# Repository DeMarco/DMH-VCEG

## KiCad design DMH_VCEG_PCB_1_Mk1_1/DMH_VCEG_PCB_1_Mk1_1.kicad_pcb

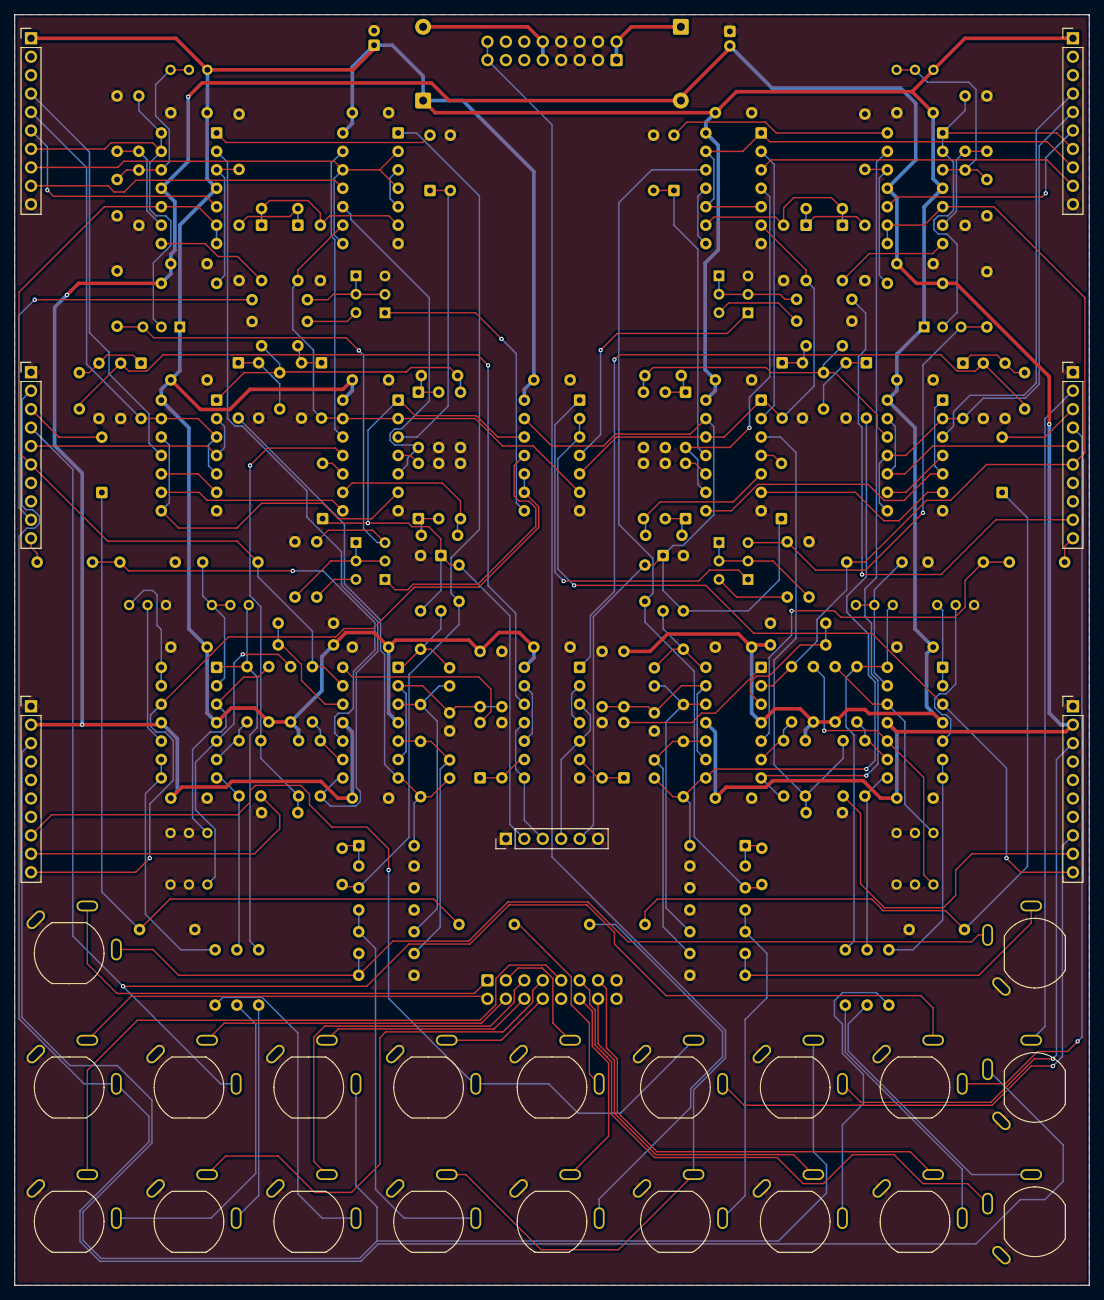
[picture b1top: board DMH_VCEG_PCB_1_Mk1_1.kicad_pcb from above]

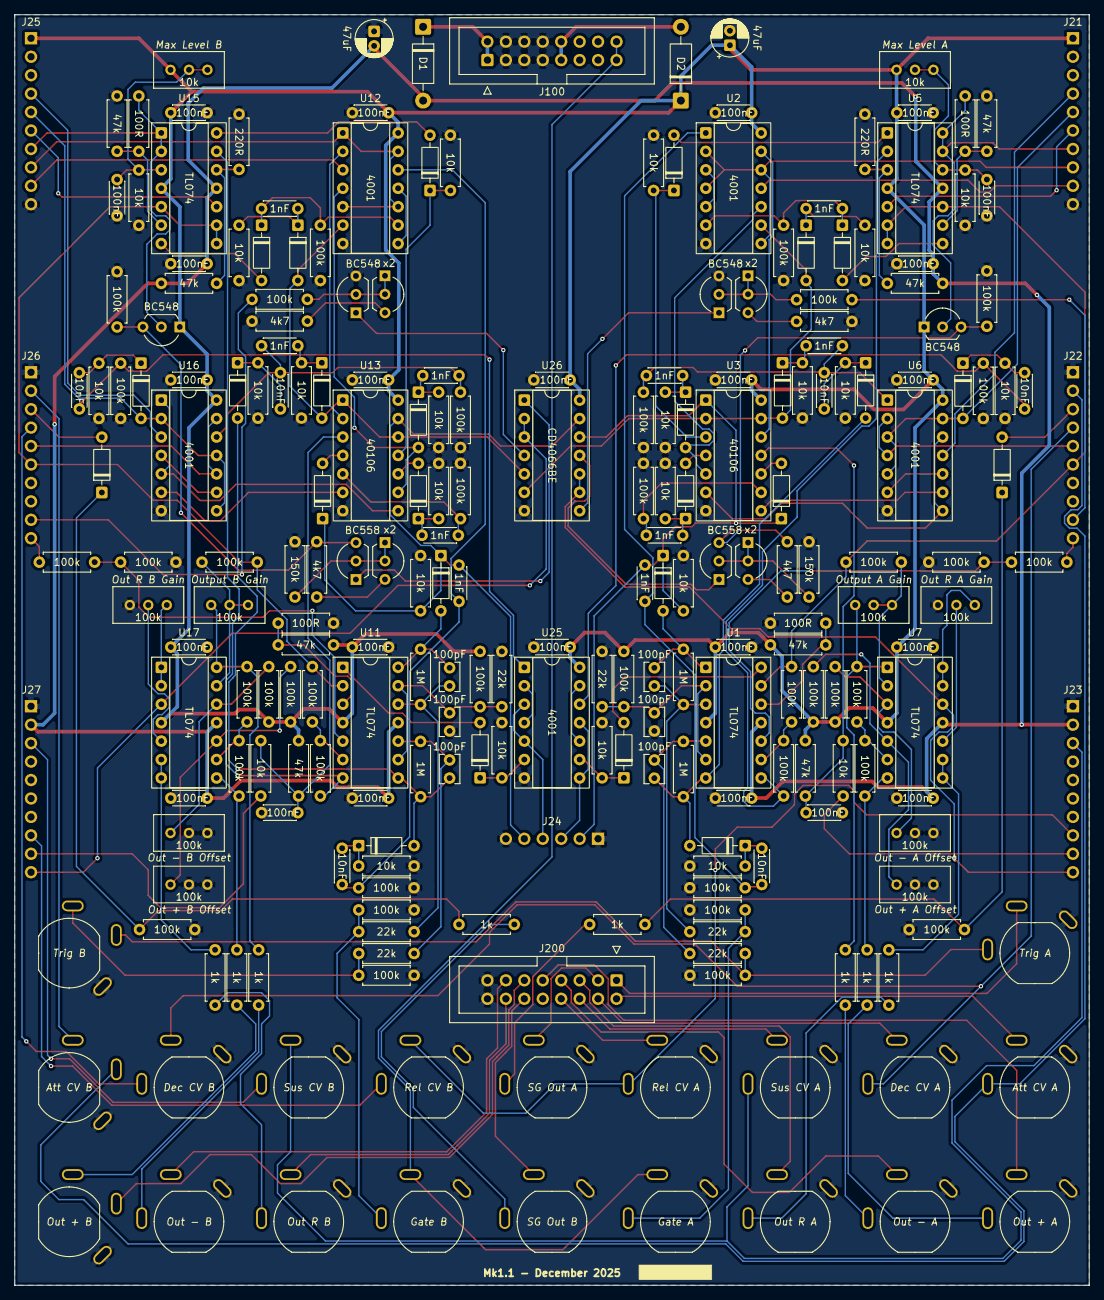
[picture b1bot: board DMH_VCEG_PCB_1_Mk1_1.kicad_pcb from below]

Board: 2 copper layers, 148.0 x 175.0 mm, 241 parts (214 on the bottom side), 183 nets.

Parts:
C1, C2: 47uF; CP_Radial_D5.0mm_P2.00mm
C3, C4, C5, C6, C8, C9, C10, C11, C12, C22, C23, C24, C25, C27, C28, C29, C30, C31, C42, C53, C58, C69, C72, C79: 100nF; C_Disc_D4.3mm_W1.9mm_P5.00mm
C41, C44, C48, C57, C60, C64: 100pF; C_Disc_D3.8mm_W2.6mm_P2.50mm
C43, C56, C59, C77, C78, C80: 10nF; C_Disc_D4.3mm_W1.9mm_P5.00mm
C46, C47, C52, C54, C55, C62, C63, C68, C70, C71: 1nF; C_Disc_D4.3mm_W1.9mm_P5.00mm
D1, D2: SB140; D_DO-41_SOD81_P10.16mm_Horizontal
D3, D4, D5, D6, D7, D12, D13, D14, D15, D16, D22, D23, D24, D25, D26, D31, D32, D33, D34, D35, D41, D42, D43, D44, D45, D46: 1N4148; D_DO-35_SOD27_P7.62mm_Horizontal
J1, J2, J3, J4, J5, J6, J7, J8, J9, J10, J11, J12, J13, J14, J15, J16, J17, J18, J19, J20: TS_Jack_6.35mm_Sw; CUI_MJ-63052A
J21, J22, J23, J25, J26, J27: Conn_01x10_PinHeader; PinHeader_1x10_P2.54mm_Vertical
J24: Conn_01x06_PinHeader; PinHeader_1x06_P2.54mm_Vertical
J100: IDC_02x08; IDC-Header_2x08_P2.54mm_Vertical_Eurorack
J200: IDC_02x08; IDC-Header_2x08_P2.54mm_Vertical_BackBone
Q1, Q2, Q17, Q18: BC558; TO-92L_Inline_Wide
Q3, Q4, Q5, Q6, Q19, Q20: BC548; TO-92L_Inline_Wide
R1, R10, R98, R107: 4k7; R_Axial_DIN0207_L6.3mm_D2.5mm_P7.62mm_Horizontal
R2, R3, R12, R14, R16, R21, R26, R36, R37, R39, R40, R42, R46, R92, R93, R94, R96, R97, R99, R100, R109, R111, R113, R118, R123, R129, R133, R134, R136, R137, R139, R143, R189, R190, R191, R193, R194, R200, R201, R202: 100k; R_Axial_DIN0207_L6.3mm_D2.5mm_P7.62mm_Horizontal
R4, R19, R34, R41, R101, R131, R138, R196: 47k; R_Axial_DIN0207_L6.3mm_D2.5mm_P7.62mm_Horizontal
R5, R23, R102, R120: 1M; R_Axial_DIN0207_L6.3mm_D2.5mm_P7.62mm_Horizontal
R6, R22, R91, R95, R103, R119, R188, R192: 1k; R_Axial_DIN0207_L6.3mm_D2.5mm_P7.62mm_Horizontal
R7, R13, R24, R25, R31, R32, R35, R38, R43, R45, R47, R104, R108, R110, R115, R116, R121, R122, R128, R132, R135, R140, R142, R144: 10k; R_Axial_DIN0207_L6.3mm_D2.5mm_P7.62mm_Horizontal
R8, R105: 150k; R_Axial_DIN0207_L6.3mm_D2.5mm_P7.62mm_Horizontal
R9, R17, R20, R106, R114, R117: 22k; R_Axial_DIN0207_L6.3mm_D2.5mm_P7.62mm_Horizontal
R33, R130, R195, R199: 100R; R_Axial_DIN0207_L6.3mm_D2.5mm_P7.62mm_Horizontal
R44, R141: 220R; R_Axial_DIN0207_L6.3mm_D2.5mm_P7.62mm_Horizontal
RV1, RV19, RV20, RV21, RV22, RV40, RV41, RV42: 100k; Potentiometer_Bourns_3296W_Vertical
RV3, RV24: 10k; Potentiometer_Bourns_3296W_Vertical
U1, U5, U7, U11, U15, U17: TL074; DIP-14_W7.62mm_Socket
U2, U6, U12, U16, U25: 4001; DIP-14_W7.62mm_Socket
U3, U13: 40106; DIP-14_W7.62mm_Socket
U26: CD4066BE; DIP-14_W7.62mm_Socket

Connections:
+12V: C2.1, C3.1, C5.1, C6.1, C8.1, C10.1, C11.1, C22.1, C24.1, C25.1, C27.1, C29.1, C30.1, C72.1, C79.1, D2.1 (K), J21.1, J25.1, Q5.1 (C), Q6.1 (C), R4.1, R16.2, R34.1, R96.2, R97.2, R101.1, R113.2, R131.1, R193.2, R194.2, RV3.3, RV24.3, U1.4 (V+), U2.14 (VDD), U3.14 (VDD), U5.4 (V+), U6.14 (VDD), U7.4 (V+), U11.4 (V+), U12.14 (VDD), U13.14 (VDD), U15.4 (V+), U16.14 (VDD), U17.4 (V+), U25.14 (VDD), U26.14 (V_{DD})
-12V: C1.2, C4.2, C9.2, C12.2, C23.2, C28.2, C31.2, D1.2 (A), J23.2, J27.2, R41.1, R138.2, U1.11 (V-), U5.11 (V-), U7.11 (V-), U11.11 (V-), U15.11 (V-), U17.11 (V-)
/CV Processing A/Max Level: J21.7, Q5.2 (B), R195.2, U5.13 (-), U5.14
/CV Processing A/Rel Proc CV: J22.9, R2.1
/CV Processing A/Sus Level: J22.10, R40.1
/CV Processing B/Max Level: J25.7, Q6.2 (B), R199.2, U15.1, U15.2 (-)
/CV Processing B/Rel Proc CV: J26.9, R99.1
/CV Processing B/Sus Level: J26.10, R137.1
/Core Circuit A/Att_State: J21.8, U2.2, U2.4, U2.8, U2.12
/Core Circuit A/Dec: D14.2 (A), U2.10, U3.5
/Core Circuit A/Dec_State: J21.4, U6.11
/Core Circuit A/Gate: J5.T, R20.2, R21.2
/Core Circuit A/Inv Sus State: J22.5, U6.2, U6.4
/Core Circuit A/InvGate: D6.2 (A), D12.2 (A), U2.9, U3.2, U3.13, U26.6
/Core Circuit A/Out: J22.6, R36.2, R93.1, U1.13 (-), U5.6 (-), U5.7, U5.10 (+)
/Core Circuit A/Out R: J8.T, R22.1
/Core Circuit A/ProcGate: C46.1, D3.1 (K), D5.1 (K), J24.2, R24.2, U3.1, U26.12
/Core Circuit A/Rel_State: J21.9, U2.11
/Core Circuit A/Sus_Reset: C52.2, C54.2, C77.2, R39.1, U6.1
/Core Circuit A/Sus_State: D43.2 (A), J21.5, U6.3, U6.5, U6.13
/Core Circuit A/Trig: J6.T, J16.TN, R9.2, R12.2
/Core Circuit B/Att_State: J25.8, U12.1, U12.5, U12.10, U12.13
/Core Circuit B/Dec: D33.2 (A), U12.4, U13.9
/Core Circuit B/Dec_State: J25.4, U16.3
/Core Circuit B/Gate: J15.T, R117.2, R118.2
/Core Circuit B/Inv Sus State: J26.5, U16.10, U16.13
/Core Circuit B/InvGate: D25.2 (A), D31.2 (A), U12.6, U13.1, U13.12, U26.5
/Core Circuit B/Out: J26.6, R133.2, R190.1, U11.2 (-), U15.5 (+), U15.8, U15.9 (-)
/Core Circuit B/Out R: J18.T, R119.1
/Core Circuit B/ProcGate: C62.1, D22.1 (K), D24.1 (K), J24.5, R121.2, U13.13, U26.13
/Core Circuit B/Rel_State: J25.9, U12.3
/Core Circuit B/Sus_Reset: C68.2, C70.2, C78.2, R136.1, U16.12
/Core Circuit B/Sus_State: D44.2 (A), J25.5, U16.2, U16.8, U16.11
/Core Circuit B/Trig: J16.T, R106.2, R109.2
/Inputs and Outputs A/Att CV A T: J1.T, J11.TN, J22.2
/Inputs and Outputs A/Dec CV A T: J2.T, J12.TN, J22.4
/Inputs and Outputs A/Gate A TN: J5.TN, J15.TN, J100.8a, J100.8b
/Inputs and Outputs A/Out + B: J20.TN, J200.6
/Inputs and Outputs A/Out - B: J19.TN, J200.7
/Inputs and Outputs A/Out R B: J18.TN, J200.15
/Inputs and Outputs A/Rel CV A T: J4.T, J14.TN, J23.8
/Inputs and Outputs A/SG Out B: J17.TN, J200.14
/Inputs and Outputs A/Sus CV A T: J3.T, J13.TN, J23.3
GND: C1.1, C2.2, C3.2, C4.1, C5.2, C6.2, C8.2, C9.1, C10.2, C11.2, C12.1, C22.2, C23.1, C24.2, C25.2, C27.2, C28.1, C29.2, C30.2, C31.1, C42.2, C44.1, C53.1, C58.2, C60.1, C69.1, C72.2, C79.2, J1.S, J2.S, J3.S, J4.S, J5.S, J6.S, J7.S, J8.S, J9.S, J10.S, J11.S, J12.S, J13.S, J14.S, J15.S, J16.S, J17.S, J18.S, J19.S, J20.S, J21.10, J22.1, J23.1, J24.1, J24.6, J25.10, J26.1, J27.1, J100.2a, J100.2b, J100.3a, J100.3b, J100.4a, J100.4b, J200.8, J200.16, Q4.3 (E), Q20.3 (E), R3.1, R8.2, R10.1, R12.1, R13.1, R14.1, R17.2, R19.1, R21.1, R24.1, R25.1, R26.1, R31.2, R32.1, R33.2, R35.1, R38.2, R39.2, R42.2, R43.1, R44.1, R45.2, R46.2, R47.2, R100.2, R105.2, R107.1, R108.1, R109.1, R110.1, R111.1, R114.1, R115.1, R116.1, R118.1, R121.1, R122.1, R123.1, R128.2, R129.2, R130.2, R132.1, R135.2, R136.2, R139.2, R140.1, R141.2, R142.2, R143.2, R144.2, R196.1, R200.2, R201.2, R202.1, RV1.1, RV20.2, RV20.3, RV21.2, RV21.3, RV22.1, RV41.2, RV41.3, RV42.2, RV42.3, U2.7 (VSS), U3.7 (VSS), U6.7 (VSS), U12.7 (VSS), U13.7 (VSS), U16.7 (VSS), U25.7 (VSS), U26.7 (V_{SS})
unnamed: C42.1, R4.2, R7.2, U3.11
unnamed: C43.2, C46.2, R14.2, U2.1
unnamed: C55.2, R46.1, U3.9
unnamed: C56.1, R129.1, U25.1
unnamed: C58.1, R101.2, R104.2, U13.3
unnamed: C59.2, C62.2, R111.2, U12.12
unnamed: C71.2, R143.1, U13.5
unnamed: C80.1, R201.1, U25.12
unnamed: D1.1 (K), J100.1a, J100.1b
unnamed: D2.2 (A), J100.5a, J100.5b
unnamed: D3.2 (A), U3.10
unnamed: C41.2, D4.2 (A), D41.2 (A), R5.1, U1.7
unnamed: C43.1, D4.1 (K), R13.2
unnamed: C48.2, D5.2 (A), R23.1, U1.1
unnamed: C47.1, D6.1 (K), R25.2
unnamed: D7.2 (A), U5.8
unnamed: C47.2, D7.1 (K), R26.2, U2.6
unnamed: C52.1, D12.1 (K), R31.1
unnamed: D13.2 (A), U1.14
unnamed: D13.1 (K), R32.2, U25.9
unnamed: C54.1, D14.1 (K), R38.1
unnamed: D15.2 (A), U5.1
unnamed: D15.1 (K), R47.1, U3.3
unnamed: D16.2 (A), U3.4
unnamed: C55.1, D16.1 (K), R45.1
unnamed: D22.2 (A), U13.4
unnamed: C57.2, D23.2 (A), D42.2 (A), R102.1, U11.8
unnamed: C59.1, D23.1 (K), R110.2
unnamed: C64.2, D24.2 (A), R120.1, U11.14
unnamed: C63.1, D25.1 (K), R122.2
unnamed: D26.2 (A), U15.7
unnamed: C63.2, D26.1 (K), R123.2, U12.9
unnamed: C68.1, D31.1 (K), R128.1
unnamed: D32.2 (A), U11.1
unnamed: D32.1 (K), R43.2, U25.6
unnamed: C70.1, D33.1 (K), R135.1
unnamed: D34.2 (A), U15.14
unnamed: D34.1 (K), R144.1, U13.11
unnamed: D35.2 (A), U13.10
unnamed: C71.1, D35.1 (K), R142.1
unnamed: C77.1, D41.1 (K), R108.2
unnamed: C78.1, D42.1 (K), R115.2
unnamed: C80.2, D43.1 (K), R116.2
unnamed: C56.2, D44.1 (K), R140.2
unnamed: D45.2 (A), J22.3
unnamed: D45.1 (K), R6.2, R100.1
unnamed: D46.2 (A), J26.3
unnamed: D46.1 (K), R103.2, R200.1
unnamed: J7.T, R6.1
unnamed: J9.T, R91.2
unnamed: J10.T, R95.2
unnamed: J17.T, R103.1
unnamed: J19.T, R188.2
unnamed: J20.T, R192.2
unnamed: J21.6, U5.5 (+)
unnamed: J23.9, R7.1
unnamed: J23.10, U7.12 (+), U26.9, U26.10
unnamed: J24.3, U25.8, U25.11
unnamed: J24.4, U25.3, U25.5
unnamed: J25.6, U15.10 (+)
unnamed: J11.T, J26.2
unnamed: J12.T, J26.4
unnamed: J13.T, J27.3
unnamed: J14.T, J27.8
unnamed: J27.9, R104.1
unnamed: J27.10, U17.3 (+), U26.2, U26.3
unnamed: J6.TN, J200.1
unnamed: J7.TN, J200.2
unnamed: J8.TN, J200.3
unnamed: J9.TN, J200.4
unnamed: J10.TN, J200.5
unnamed: J1.TN, J200.9
unnamed: J2.TN, J200.10
unnamed: J3.TN, J200.11
unnamed: J4.TN, J200.12
unnamed: Q1.1 (C), Q1.2 (B), Q2.2 (B), R8.1
unnamed: Q1.3 (E), R1.2
unnamed: Q2.1 (C), U26.11
unnamed: Q2.3 (E), Q5.3 (E), R1.1, R202.2
unnamed: Q3.1 (C), Q3.2 (B), Q4.2 (B), R2.2
unnamed: Q3.3 (E), R10.2
unnamed: Q4.1 (C), U26.8
unnamed: Q17.1 (C), Q17.2 (B), Q18.2 (B), R105.1
unnamed: Q17.3 (E), R98.2
unnamed: Q18.1 (C), U26.1
unnamed: Q6.3 (E), Q18.3 (E), R3.2, R98.1
unnamed: Q19.1 (C), Q19.2 (B), Q20.2 (B), R99.2
unnamed: Q19.3 (E), R107.2
unnamed: Q20.1 (C), U26.4
unnamed: R91.1, R94.1, RV19.1, U7.1
unnamed: R92.2, R95.1, U7.7
unnamed: R188.1, R191.1, RV40.1, U17.14
unnamed: R189.2, R192.1, U17.8
unnamed: C48.1, R20.1, R23.2, U1.3 (+)
unnamed: C44.2, R16.1, R17.1, U1.2 (-), U1.6 (-)
unnamed: C41.1, R5.2, R9.1, U1.5 (+)
unnamed: R40.2, R42.1, U1.10 (+)
unnamed: R36.1, R37.2, U1.9 (-)
unnamed: R33.1, R34.2, U1.12 (+)
unnamed: U2.3, U2.5
unnamed: U2.13, U3.12
unnamed: U3.6, U6.8, U6.12
unnamed: U3.8, U6.9
unnamed: R41.2, R44.2, U5.3 (+)
unnamed: R37.1, U1.8, U5.2 (-)
unnamed: R195.1, R196.2, U5.9 (-)
unnamed: C53.2, R35.2, RV3.1, RV3.2, U5.12 (+)
unnamed: U6.6, U6.10
unnamed: R96.1, RV20.1, U7.3 (+)
unnamed: R93.2, RV19.2, RV19.3, U7.2 (-)
unnamed: R97.1, RV21.1, U7.5 (+)
unnamed: R92.1, R94.2, U7.6 (-)
unnamed: RV1.2, U7.10 (+)
unnamed: R22.2, U7.8, U7.9 (-)
unnamed: RV1.3, U7.13 (-), U7.14
unnamed: R130.1, R131.2, U11.3 (+)
unnamed: R137.2, R139.1, U11.5 (+)
unnamed: R133.1, R134.2, U11.6 (-)
unnamed: C57.1, R102.2, R106.1, U11.10 (+)
unnamed: C60.2, R113.1, R114.2, U11.9 (-), U11.13 (-)
unnamed: C64.1, R117.1, R120.2, U11.12 (+)
unnamed: U12.2, U13.2
unnamed: U12.8, U12.11
unnamed: U13.6, U16.6
unnamed: U13.8, U16.1, U16.5
unnamed: C69.2, R132.2, RV24.1, RV24.2, U15.3 (+)
unnamed: R19.2, R199.1, U15.6 (-)
unnamed: R138.1, R141.1, U15.12 (+)
unnamed: R134.1, U11.7, U15.13 (-)
unnamed: U16.4, U16.9
unnamed: RV22.3, U17.1, U17.2 (-)
unnamed: RV22.2, U17.5 (+)
unnamed: R119.2, U17.6 (-), U17.7
unnamed: R194.1, RV42.1, U17.10 (+)
unnamed: R189.1, R191.2, U17.9 (-)
unnamed: R193.1, RV41.1, U17.12 (+)
unnamed: R190.2, RV40.2, RV40.3, U17.13 (-)
unnamed: U25.2, U25.4
unnamed: U25.10, U25.13

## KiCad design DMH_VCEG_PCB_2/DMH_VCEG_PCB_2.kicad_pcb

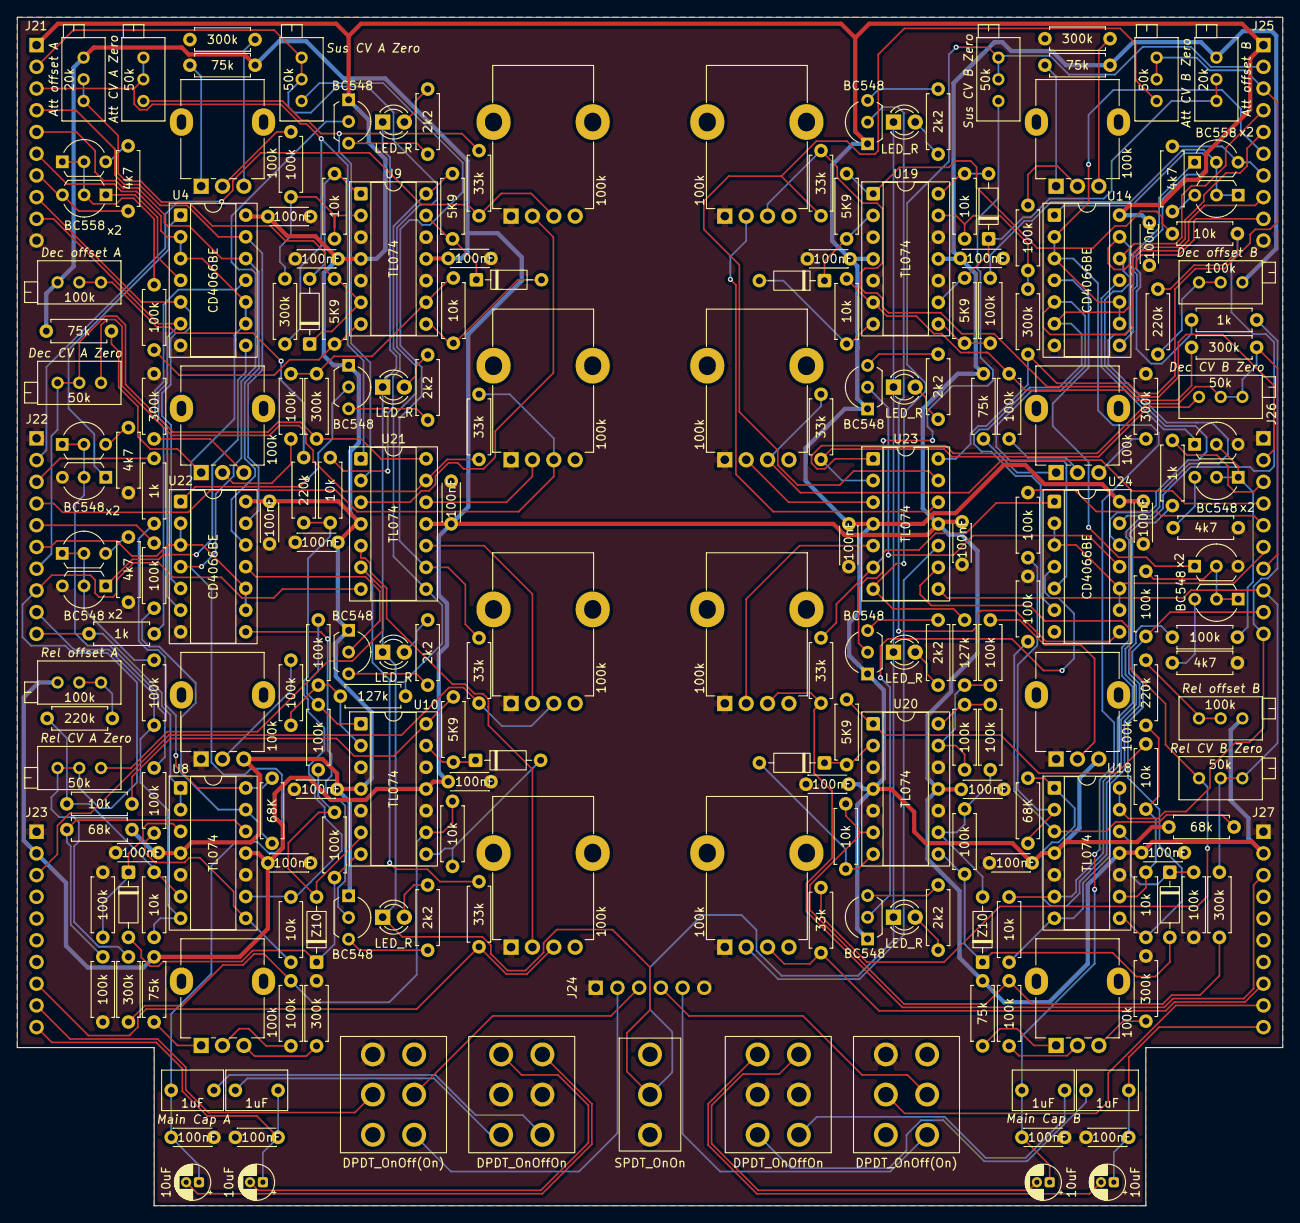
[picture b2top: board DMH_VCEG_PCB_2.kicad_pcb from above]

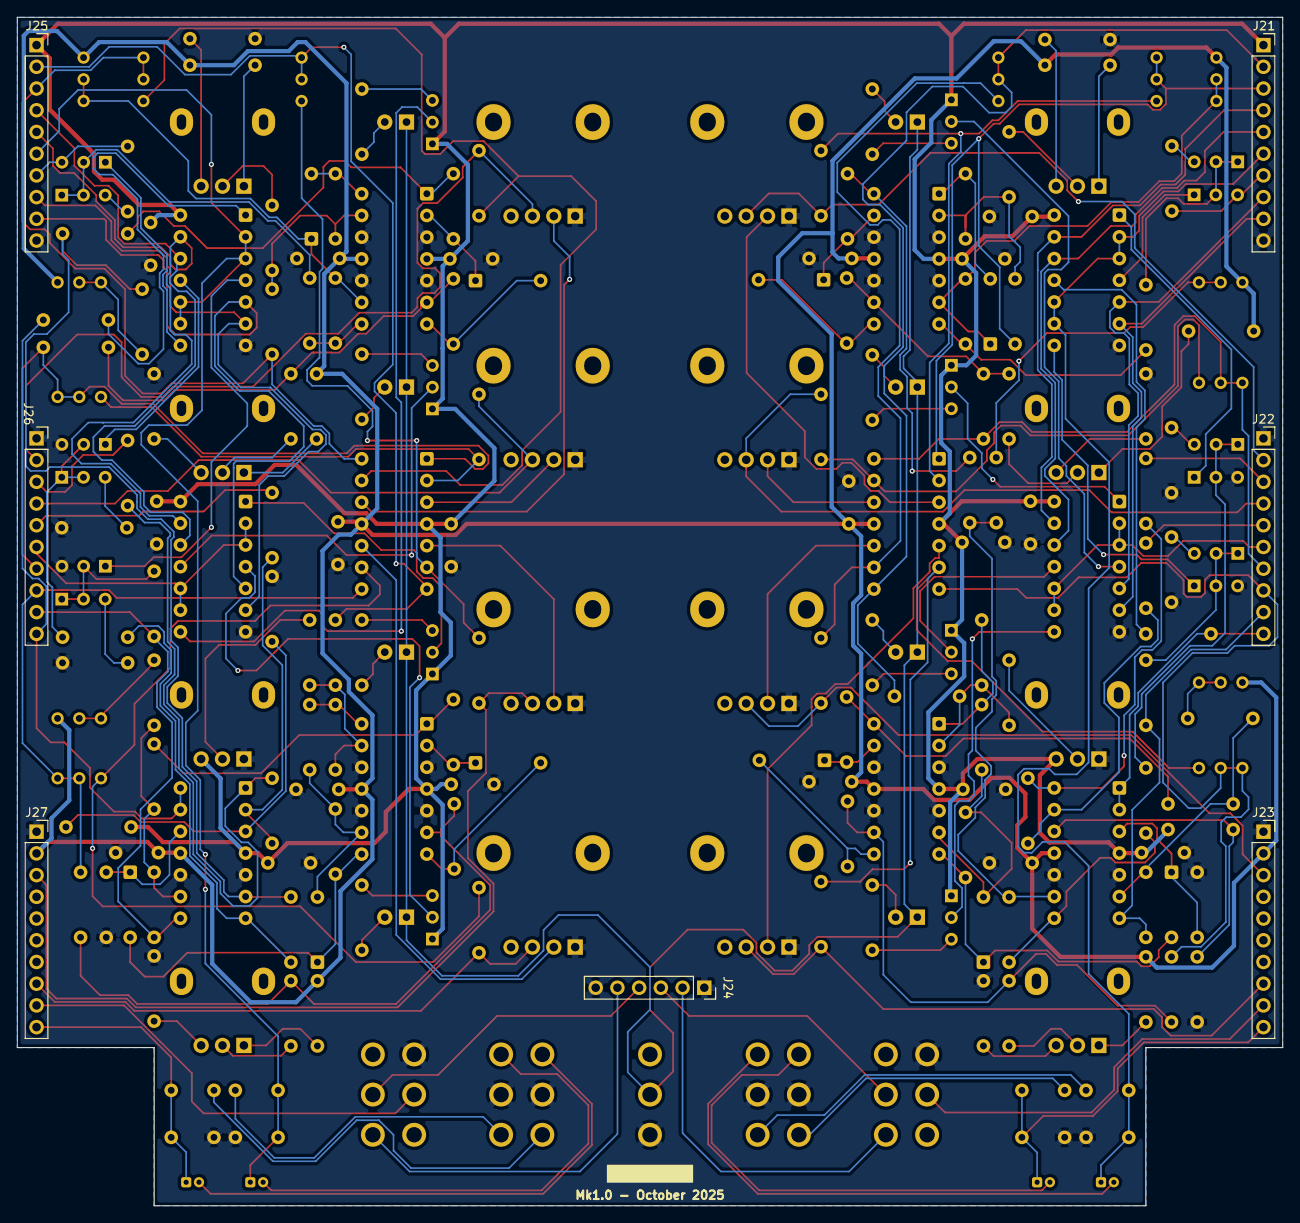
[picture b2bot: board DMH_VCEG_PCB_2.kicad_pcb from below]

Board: 2 copper layers, 148.0 x 139.0 mm, 224 parts (7 on the bottom side), 188 nets.

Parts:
C7, C13, C14, C15, C16, C17, C18, C19, C20, C21, C26, C32, C33, C34, C35, C36, C37, C38, C39, C40, C73, C74, C75, C76: 100nF; C_Disc_D4.3mm_W1.9mm_P5.00mm
C45, C50, C61, C66: 1uF; C_Rect_L7.0mm_W4.5mm_P5.00mm
C49, C51, C65, C67: 10uF; CP_Radial_D4.0mm_P1.50mm
D8, D9, D10, D11, D27, D28, D29, D30: LED_R; LED_D3.0mm
D17, D18, D20, D21, D36, D37, D39, D40: 1N4148; D_DO-35_SOD27_P7.62mm_Horizontal
D19, D38: Z10; D_DO-35_SOD27_P7.62mm_Horizontal
J21, J22, J23, J25, J26, J27: Conn_01x10_PinHeader; PinSocket_1x10_P2.54mm_Vertical
J24: Conn_01x06_PinHeader; PinSocket_1x06_P2.54mm_Vertical
Q7, Q8, Q9, Q10, Q13, Q14, Q15, Q16, Q23, Q24, Q25, Q26, Q29, Q30, Q31, Q32: BC548; TO-92L_Inline_Wide
Q11, Q12, Q27, Q28: BC558; TO-92L_Inline_Wide
R11, R53, R54, R62, R64, R68, R69, R70, R71, R72, R79, R81, R89, R150, R151, R159, R161, R165, R166, R167, R168, R169, R176, R178, R186, R198: 100k; R_Axial_DIN0207_L6.3mm_D2.5mm_P7.62mm_Horizontal
R15, R90, R112, R187: 1k; R_Axial_DIN0207_L6.3mm_D2.5mm_P7.62mm_Horizontal
R18, R197: 68k; R_Axial_DIN0207_L6.3mm_D2.5mm_P7.62mm_Horizontal
R27, R28, R29, R30, R124, R125, R126, R127: 2k2; R_Axial_DIN0207_L6.3mm_D2.5mm_P7.62mm_Horizontal
R48, R55, R56, R65, R73, R82, R145, R152, R153, R162, R170, R179: 300k; R_Axial_DIN0207_L6.3mm_D2.5mm_P7.62mm_Horizontal
R49, R58, R75, R146, R155, R172: 75k; R_Axial_DIN0207_L6.3mm_D2.5mm_P7.62mm_Horizontal
R50, R59, R61, R63, R76, R78, R80, R147, R156, R158, R160, R173, R175, R177: 10k; R_Axial_DIN0207_L6.3mm_D2.5mm_P7.62mm_Horizontal
R51, R66, R83, R148, R163, R180: 4k7; R_Axial_DIN0207_L6.3mm_D2.5mm_P7.62mm_Horizontal
R52, R60, R77, R149, R157, R174: 5K9; R_Axial_DIN0207_L6.3mm_D2.5mm_P7.62mm_Horizontal
R57, R74, R154, R171: 220k; R_Axial_DIN0207_L6.3mm_D2.5mm_P7.62mm_Horizontal
R67, R164: 127k; R_Axial_DIN0207_L6.3mm_D2.5mm_P7.62mm_Horizontal
R84, R85, R86, R87, R181, R182, R183, R184: 33k; R_Axial_DIN0207_L6.3mm_D2.5mm_P7.62mm_Horizontal
R88, R185: 68K; R_Axial_DIN0207_L6.3mm_D2.5mm_P7.62mm_Horizontal
RV4, RV25: 20k; Potentiometer_Bourns_3296X_Horizontal
RV5, RV7, RV8, RV10, RV26, RV28, RV29, RV31: 100k; Potentiometer_Alpha_RD901F-40-00D_Single_Vertical
RV6, RV9, RV27, RV30: 100k; Potentiometer_Bourns_3296X_Horizontal
RV11, RV13, RV15, RV17, RV32, RV34, RV36, RV38: 50k; Potentiometer_Bourns_3296X_Horizontal
RV12, RV14, RV16, RV18, RV33, RV35, RV37, RV39: 100k; Potentiometer_TT_P110KH1
SW1, SW5: DPDT_OnOff(On); Toggle_Switch_2_Poles_TE
SW2, SW4: DPDT_OnOffOn; Toggle_Switch_2_Poles_TE
SW3: SPDT_OnOn; Toggle_Switch_TE
U4, U14, U22, U24: CD4066BE; DIP-14_W7.62mm_Socket
U8, U9, U10, U18, U19, U20, U21, U23: TL074; DIP-14_W7.62mm_Socket

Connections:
+12V: C7.1, C13.1, C15.1, C17.1, C19.1, C21.1, C26.1, C32.1, C34.1, C36.1, C38.1, C40.1, J21.1, J25.1, Q7.1 (C), Q8.1 (C), Q9.1 (C), Q10.1 (C), Q23.1 (C), Q24.1 (C), Q25.1 (C), Q26.1 (C), R18.1, R197.1, RV8.3, RV29.3, U4.14 (V_{DD}), U8.4 (V+), U9.4 (V+), U10.4 (V+), U14.14 (V_{DD}), U18.4 (V+), U19.4 (V+), U20.4 (V+), U21.4 (V+), U22.14 (V_{DD}), U23.4 (V+), U24.14 (V_{DD})
-12V: C14.2, C16.2, C18.2, C20.2, C33.2, C35.2, C37.2, C39.2, J23.2, J27.2, R49.2, R58.2, R75.2, R146.2, R155.2, R172.2, RV4.3, RV6.3, RV9.3, RV25.3, RV27.3, RV30.3, U8.11 (V-), U9.11 (V-), U10.11 (V-), U18.11 (V-), U19.11 (V-), U20.11 (V-), U21.11 (V-), U23.11 (V-)
/CV Processing A/Att CV: J21.3, R48.2, RV11.2, RV11.3, U21.1
/CV Processing A/Att Cur Src: Q12.1 (C), U4.4
/CV Processing A/Dec CV: J22.7, R56.2, RV13.2, RV13.3, U21.14
/CV Processing A/Dec Cur Snk: Q14.1 (C), U4.1
/CV Processing A/Max Level: J21.7, Q12.3 (E), R51.2
/CV Processing A/Rel CV: J22.8, R73.2, RV17.2, RV17.3, U21.7
/CV Processing A/Rel Cur Snk: Q16.1 (C), U4.8
/CV Processing A/Rel Proc CV: J22.9, R78.2, R81.1, U8.7
/CV Processing A/Sus CV: J21.2, R67.1, RV15.2, RV15.3, U21.8
/CV Processing A/Sus Level: J22.10, R15.2, U8.1, U8.2 (-)
/CV Processing B/Att CV: J25.3, R145.2, RV32.2, RV32.3, U23.14
/CV Processing B/Att Cur Src: Q28.1 (C), U14.8
/CV Processing B/Dec CV: J26.7, R153.2, RV34.2, RV34.3, U23.1
/CV Processing B/Dec Cur Snk: Q30.1 (C), U14.11
/CV Processing B/Max Level: J25.7, Q28.3 (E), R148.2
/CV Processing B/Rel CV: J26.8, R170.2, RV38.2, RV38.3, U23.8
/CV Processing B/Rel Cur Snk: Q32.1 (C), U14.4
/CV Processing B/Rel Proc CV: J26.9, R175.2, R178.1, U18.8
/CV Processing B/Sus CV: J25.2, R164.1, RV36.2, RV36.3, U23.7
/CV Processing B/Sus Level: J26.10, R112.2, U18.13 (-), U18.14
/Core Circuit A/Att_State: J21.8, U4.5, U22.5
/Core Circuit A/Dec_State: J21.4, U4.13, U22.13
/Core Circuit A/Inv Sus State: J22.5, R89.1
/Core Circuit A/LEDs SW: D8.1 (K), D9.1 (K), D10.1 (K), D11.1 (K), D27.1 (K), D28.1 (K), D29.1 (K), D30.1 (K), SW3.2 (B)
/Core Circuit A/Out: J22.6, U22.2, U22.3, U22.9, U22.10
/Core Circuit A/ProcGate: J24.2, SW1.3 (C)
/Core Circuit A/Rel_State: J21.9, U4.6, U22.6
/Core Circuit A/Sus_State: J21.5, U4.12, U22.12
/Core Circuit B/Att_State: J25.8, U14.6, U24.6
/Core Circuit B/Dec_State: J25.4, U14.12, U24.12
/Core Circuit B/Inv Sus State: J26.5, R186.1
/Core Circuit B/Out: J26.6, U24.2, U24.3, U24.9, U24.10
/Core Circuit B/ProcGate: J24.5, SW5.3 (C)
/Core Circuit B/Rel_State: J25.9, U14.5, U24.5
/Core Circuit B/Sus_State: J25.5, U14.13, U24.13
GND: C7.2, C13.2, C14.1, C15.2, C16.1, C17.2, C18.1, C19.2, C20.1, C21.2, C26.2, C32.2, C33.1, C34.2, C35.1, C36.2, C37.1, C38.2, C39.1, C40.2, C73.1, C74.1, C75.1, C76.1, J21.10, J22.1, J23.1, J24.1, J24.6, J25.10, J26.1, J27.1, Q14.3 (E), Q16.3 (E), Q30.3 (E), Q32.3 (E), R11.2, R55.1, R65.1, R66.1, R69.1, R82.1, R83.1, R152.1, R162.1, R163.1, R166.1, R179.1, R180.1, R198.2, RV8.1, RV12.1, RV14.1, RV16.1, RV18.1, RV29.1, RV33.1, RV35.1, RV37.1, RV39.1, SW1.4 (A), SW2.2 (B), SW2.5 (B), SW3.1 (C), SW4.2 (B), SW4.5 (B), SW5.4 (A), U4.7 (V_{SS}), U8.5 (+), U8.10 (+), U9.3 (+), U9.5 (+), U9.10 (+), U9.12 (+), U10.3 (+), U10.5 (+), U10.10 (+), U10.12 (+), U14.7 (V_{SS}), U18.5 (+), U18.10 (+), U19.3 (+), U19.5 (+), U19.10 (+), U19.12 (+), U20.3 (+), U20.5 (+), U20.10 (+), U20.12 (+), U22.7 (V_{SS}), U24.7 (V_{SS})
unnamed: D8.2 (A), R27.2
unnamed: D9.2 (A), R28.2
unnamed: D10.2 (A), R29.2
unnamed: D11.2 (A), R30.2
unnamed: D17.2 (A), R50.2, U9.1
unnamed: D17.1 (K), R52.1, RV4.1, RV4.2, U9.6 (-)
unnamed: D18.2 (A), R59.2, U9.8
unnamed: D18.1 (K), R60.1, U9.13 (-)
unnamed: D19.2 (A), R70.2, R71.1, U10.6 (-)
unnamed: D19.1 (K), D20.2 (A), R71.2, U10.7
unnamed: D20.1 (K), R69.2, U8.3 (+)
unnamed: D21.2 (A), R76.2, U10.8
unnamed: D21.1 (K), R77.1, U10.13 (-)
unnamed: D27.2 (A), R124.2
unnamed: D28.2 (A), R125.2
unnamed: D29.2 (A), R126.2
unnamed: D30.2 (A), R127.2
unnamed: D36.2 (A), R147.2, U19.14
unnamed: D36.1 (K), R149.1, RV25.1, RV25.2, U19.9 (-)
unnamed: D37.2 (A), R156.2, U19.7
unnamed: D37.1 (K), R157.1, U19.2 (-)
unnamed: D38.2 (A), R167.2, R168.1, U20.9 (-)
unnamed: D38.1 (K), D39.2 (A), R168.2, U20.8
unnamed: D39.1 (K), R166.2, U18.12 (+)
unnamed: D40.2 (A), R173.2, U20.7
unnamed: D40.1 (K), R174.1, U20.2 (-)
unnamed: C50.1, C51.1, C73.2, J21.6, U4.2, U4.3, U4.9, U4.10
unnamed: J22.2, R84.1, RV12.3
unnamed: J22.3, R90.1
unnamed: J22.4, R85.1, RV14.3
unnamed: J23.3, R86.1, RV16.3
unnamed: J23.8, R87.1, RV18.3
unnamed: J23.9, SW1.5 (B)
unnamed: C45.2, C49.1, C74.2, J23.10
unnamed: J24.3, SW1.2 (B)
unnamed: J24.4, SW5.2 (B)
unnamed: C66.1, C67.1, C75.2, J25.6, U14.2, U14.3, U14.9, U14.10
unnamed: J26.2, R181.1, RV33.3
unnamed: J26.3, R187.1
unnamed: J26.4, R182.1, RV35.3
unnamed: J27.3, R183.1, RV37.3
unnamed: J27.8, R184.1, RV39.3
unnamed: J27.9, SW5.5 (B)
unnamed: C61.2, C65.1, C76.2, J27.10
unnamed: Q7.2 (B), U22.4
unnamed: Q7.3 (E), R27.1
unnamed: Q8.2 (B), U22.1
unnamed: Q8.3 (E), R28.1
unnamed: Q9.2 (B), U22.11
unnamed: Q9.3 (E), R29.1
unnamed: Q10.2 (B), U22.8
unnamed: Q10.3 (E), R30.1
unnamed: Q11.1 (C), Q11.2 (B), Q12.2 (B), R54.2
unnamed: Q11.3 (E), R51.1
unnamed: Q13.1 (C), Q13.2 (B), Q14.2 (B), R64.2
unnamed: Q13.3 (E), R66.2
unnamed: Q15.1 (C), Q15.2 (B), Q16.2 (B), R81.2
unnamed: Q15.3 (E), R83.2
unnamed: Q23.2 (B), U24.8
unnamed: Q23.3 (E), R124.1
unnamed: Q24.2 (B), U24.11
unnamed: Q24.3 (E), R125.1
unnamed: Q25.2 (B), U24.1
unnamed: Q25.3 (E), R126.1
unnamed: Q26.2 (B), U24.4
unnamed: Q26.3 (E), R127.1
unnamed: Q27.1 (C), Q27.2 (B), Q28.2 (B), R151.2
unnamed: Q27.3 (E), R148.1
unnamed: Q29.1 (C), Q29.2 (B), Q30.2 (B), R161.2
unnamed: Q29.3 (E), R163.2
unnamed: Q31.1 (C), Q31.2 (B), Q32.2 (B), R178.2
unnamed: Q31.3 (E), R180.2
unnamed: R15.1, U4.11
unnamed: R49.1, RV5.1
unnamed: R52.2, R54.1, U9.7
unnamed: R53.1, RV5.2
unnamed: R55.2, RV5.3
unnamed: R57.2, RV6.1, RV6.2
unnamed: R58.1, RV7.1
unnamed: R60.2, R63.1, U9.14
unnamed: R61.2, R64.1, U8.8
unnamed: R62.1, RV7.2
unnamed: R65.2, RV7.3
unnamed: R68.2, R70.1, U10.1
unnamed: R72.1, RV8.2
unnamed: R74.2, RV9.1, RV9.2
unnamed: R75.1, RV10.1
unnamed: R77.2, R80.1, U10.14
unnamed: R79.1, RV10.2
unnamed: R82.2, RV10.3
unnamed: R88.2, R90.2, U8.14
unnamed: R112.1, U14.1
unnamed: R146.1, RV26.1
unnamed: R149.2, R151.1, U19.8
unnamed: R150.1, RV26.2
unnamed: R152.2, RV26.3
unnamed: R154.2, RV27.1, RV27.2
unnamed: R155.1, RV28.1
unnamed: R157.2, R160.1, U19.1
unnamed: R158.2, R161.1, U18.7
unnamed: R159.1, RV28.2
unnamed: R162.2, RV28.3
unnamed: R165.2, R167.1, U20.14
unnamed: R169.1, RV29.2
unnamed: R171.2, RV30.1, RV30.2
unnamed: R172.1, RV31.1
unnamed: R174.2, R177.1, U20.1
unnamed: R176.1, RV31.2
unnamed: R179.2, RV31.3
unnamed: R185.2, R187.2, U18.1
unnamed: C51.2, SW2.1 (A)
unnamed: C50.2, SW2.3 (C)
unnamed: C49.2, SW2.4 (A)
unnamed: C45.1, SW2.6 (C)
unnamed: C67.2, SW4.1 (A)
unnamed: C66.2, SW4.3 (C)
unnamed: C65.2, SW4.4 (A)
unnamed: C61.1, SW4.6 (C)
unnamed: R74.1, R78.1, R80.2, U8.6 (-)
unnamed: R57.1, R61.1, R63.2, U8.9 (-)
unnamed: R197.2, R198.1, U8.12 (+)
unnamed: R88.1, R89.2, U8.13 (-)
unnamed: R48.1, R50.1, R53.2, U9.2 (-)
unnamed: R56.1, R59.1, R62.2, U9.9 (-)
unnamed: R67.2, R68.1, R72.2, U10.2 (-)
unnamed: R73.1, R76.1, R79.2, U10.9 (-)
unnamed: R11.1, R18.2, U18.3 (+)
unnamed: R185.1, R186.2, U18.2 (-)
unnamed: R154.1, R158.1, R160.2, U18.6 (-)
unnamed: R171.1, R175.1, R177.2, U18.9 (-)
unnamed: R153.1, R156.1, R159.2, U19.6 (-)
unnamed: R145.1, R147.1, R150.2, U19.13 (-)
unnamed: R170.1, R173.1, R176.2, U20.6 (-)
unnamed: R164.2, R165.1, R169.2, U20.13 (-)
unnamed: RV12.2, U21.3 (+)
unnamed: R84.2, RV11.1, U21.2 (-)
unnamed: RV18.2, U21.5 (+)
unnamed: R87.2, RV17.1, U21.6 (-)
unnamed: RV16.2, U21.10 (+)
unnamed: R86.2, RV15.1, U21.9 (-)
unnamed: RV14.2, U21.12 (+)
unnamed: R85.2, RV13.1, U21.13 (-)
unnamed: RV35.2, U23.3 (+)
unnamed: R182.2, RV34.1, U23.2 (-)
unnamed: RV37.2, U23.5 (+)
unnamed: R183.2, RV36.1, U23.6 (-)
unnamed: RV39.2, U23.10 (+)
unnamed: R184.2, RV38.1, U23.9 (-)
unnamed: RV33.2, U23.12 (+)
unnamed: R181.2, RV32.1, U23.13 (-)

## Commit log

2025-03-25 Craeted KiCad projects
2025-03-25 Added hole symbols to Panel
2025-04-21 15cm Panel design in progress
2025-04-21 Front panel design in progress
2025-04-22 Finished panel design
2025-04-22 Added amplitude CV input and pot
2025-04-26 Added more features
    - Amp offset switch
    - Re-added Out -
    - Added Out R
    - Rearranged positions to make everything fit
2025-05-02 Removed built in VCA
2025-06-26 Initiated schematic design
2025-06-27 IO pages done
    Core Circuit A ongoing
2025-06-27 Core circuit schematic in progress
2025-06-28 Core Circuit A ready for breadboarding
2025-06-28 Minor corrections during breadboarding
2025-06-28 Minor correction to resistor text
    Only DPDT left to mount on breadboard
2025-07-12 Create circuitjs-VCEG-tests.txt
    Falstad simulation with A, D and R CV control determination
2025-07-12 Update circuitjs-VCEG-tests.txt
    Added Emitter-Follower for Sustain CV
2025-07-12 Updated Panel to new circuit
    Changed Exp switch function to Long.
    Added central switch to switch LEDs on and off.
2025-07-12 MFOS based core circuit in progress
2025-07-12 Working on Sus and Dec CV
2025-07-13 Tests with Sus CV ongoing
2025-07-14 Perfected Decay and Sustain CV in simulation
2025-07-14 Removed reference circuit pictures
2025-07-15 Finished Sus and Dec CV circuit
    Now simulating Attack CV circuit
2025-07-16 Fine tuned attack pot circuit
2025-07-17 Fine tuned A D and S
2025-07-18 Release control added to simulation
2025-07-18 Updated D and S circuits in schematic
2025-07-19 Updated main cap resistor to 680R
    ... in order to limit peak current that goes through it and the analog switches to ~13.5 mA instead of ~19.7 mA.
2025-07-19 Added Attack control to schematic
    ... and trimpots to adjust CV offset and range
2025-07-19 Added Release circuit to schematic
2025-07-19 Implemented SG Out A
2025-07-19 Implemented LEDs
2025-07-19 Added Out R
    Ready for breadboarding
2025-07-20 Corrected Out R design
2025-07-20 Placed Circuit B pages
2025-07-21 Reanotated schematic
2025-07-22 Reannotated ICs to match MFOS schematic
2025-07-22 Fixed inverted Out and some fp assignments
2025-07-25 SG out modifications in progress
2025-07-25 Updated SG Out circuit
2025-07-26 Added Loop circuit
2025-07-26 PCB 1 ready for placement
2025-07-26 Re-exported BoM
2025-07-26 Deleted old BoM
2025-07-27 Placed jacks and pot references
2025-07-27 Updated BoM
2025-07-29 Copied PCB 1 as PCB 2
2025-07-29 Placed front panel components on PCB 2
2025-07-30 Placed ICs and pin headers on PCB 2
2025-07-31 Addition of manual gate ongoing
2025-08-01 Copied Manual Gate circuit to PCB 1 schematic
2025-08-01 Added Output attenuation circuit
2025-08-01 Removed unnecessary trimpots
2025-08-01 Fixed mistake in IO connections
2025-08-05 Tuned Rel c-mirror to 2ms to 7s release time
2025-08-06 Optimized Release CV circuit in sim
2025-08-06 Added Attack CV to sim
2025-08-06 Added sustain and decay to sim
2025-08-08 Adaptation of CV circuits ongoing
2025-08-08 Redesigned circuit A
2025-08-09 Redesign A almost finished
    Need to update the Out R to use Release Current Mirror
2025-08-09 Finished circuit A redesign
    Except for component re-annotation
2025-08-11 Copied circuit A to B
2025-08-11 Divided components between PCB 1 and 2
    Still need to:
    - Place interface pins where needed
    - Set "exclude from board" options where needed
    - Copy schematic over to PCB 2 project
    - Invert "exclude from board" options where needed
2025-08-12 Enhanced LED control in circuit A
    Same on circuit B in progress
2025-08-12 Simulating better Out R
2025-08-13 Improved Out R attack in sim v6
2025-08-15 Reworked Out R A circuit
2025-08-16 Copied Circuit A into B
    And added diode to protect input of U3B
2025-08-16 Re-annotated whole circuit
    Now need to place interface pins and determine in and out of board settings
2025-08-16 Ready for breadboarding
2025-08-16 Synced PCB 2 project with PCB 1
2025-08-16 Started placement on PCB 2
2025-08-17 PCB 2 placement in progress
2025-08-18 Made new BoM
2025-08-19 Added breadboard layout drawing
2025-08-20 Small changes during breadboarding
2025-08-22 Updated Dec and Rel trimpots to 100k
2025-08-23 Mods on PCB 1 after breadboarding
2025-08-24 Fixed sus state detection circuit A
2025-08-25 Added fast cap selection
2025-08-27 Fixed Sus Gate output stage
2025-08-29 Modified Out R
2025-08-30 Synced changes to Circuit B
2025-08-30 Synced changes to PCB 2
2025-08-30 PCB 2 comp placement ongoing
2025-08-30 PCB 2 placement ongoing
2025-08-31 PCB 2 Placement done
2025-08-31 PCB 2 routing in progress
2025-09-01 Found better calib value for attack
2025-09-02 Breadboard based mods
2025-09-02 Updated PCB 1 with changes from breadboard tests
2025-09-03 Made flip flop for loop
2025-09-03 Iproved loop FF set
2025-09-04 Made looping robust
2025-09-05 Synced A and B changes on PCB 1
2025-09-05 Synced PCB 1 and 2
2025-09-06 Restarted component placing on Main
2025-09-08 PCB 2 Routing complete
    But still need optimization for empty areas
2025-09-08 Finished PCB 2 routing optimization
2025-09-09 Synced PCB 2 schematic to PCB 1
2025-09-09 PCB 1 placement in progress
2025-09-15 PCB 1 circuit A placement done
    ciurcuit B placement in progress
2025-09-19 PCB 1 placement done
2025-09-21 Synced PCB 1 o PCB 2
2025-09-21 PCB 1 routing in progress
2025-10-02 Routing done
2025-10-03 Optimized PCBs
2025-10-03 Generated first gerbers
    Still need to fix issues
2025-10-04 Fixing wrong DPDT polarity ongoing
2025-10-04 Fixed toggle switch orientation
    ... and regenerated gerbers
2025-10-18 Grouped symbols in BoM view
2025-10-26 Found mistake with SG Out offset resistors
2025-10-28 Created M1k.1 version of PCB 1
2025-10-28 Out R rework ongoing
2025-11-01 Changed Out R design on Circuit A
    Needs testing on breadboard
2025-11-02 Fixed normalled tip routing for CV and Gate
2025-12-23 Modified Out R output buffer
2025-12-24 Validated Out R design
    Next step is to update Circuit B with it and then respin PCB 1
2025-12-24 Copied Out R redesign to Circuit B
2025-12-24 Preping for Circuit 2 attenuverter rewire
2025-12-25 Redesigned PCB 1
2026-01-03 Added diodes to Sustain Gate outputs
2026-02-21 Re-generated PCB 1 Mk1.1 Gerbers
2026-04-12 Minor silkscreen corrections
2026-04-24 KiCad 10
2026-06-03 Reorganized repo
    - Kicad 10
    - Centralized and updated SynthStuff library
    - Simulations folder
    - Moved first version of PCB 1 to old_versions folder
    - Gerbers folder
